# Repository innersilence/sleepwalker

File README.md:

sleepwalker
===========

Pulse and oximetry sensor and graphing software

AVR based wearable wireless sensor that sends pulse/blood oxigen level over wireless link to the collecting service.

Used to monitor blood oxigeneation to detect sleep apnea, REM periods.

LICENSE: MIT

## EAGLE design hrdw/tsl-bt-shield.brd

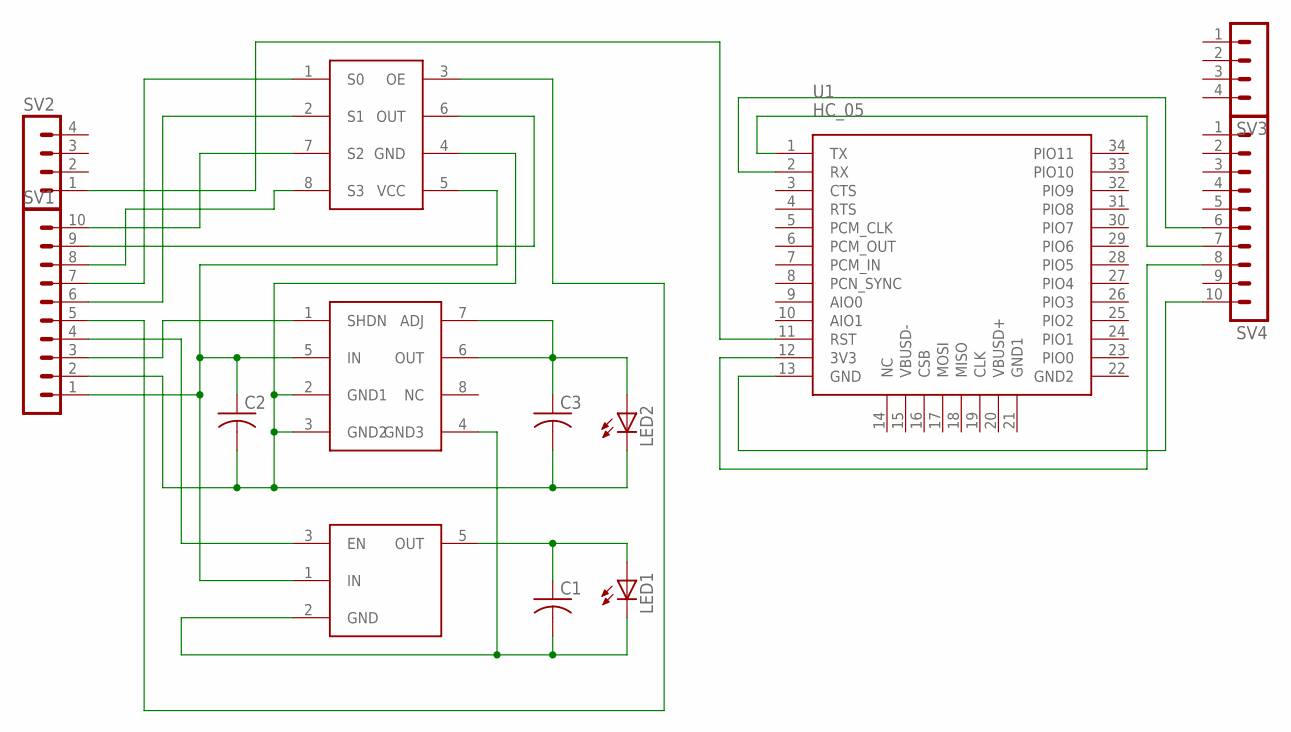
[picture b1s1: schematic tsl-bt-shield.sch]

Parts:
C1, C2, C3: C-USC1206K; C1206K
LED1, LED2: LED; SMARTLED-TTW
SV1, SV4: MA10-1
SV2, SV3: MA04-1
U1: HC_05; BLUETOOTH_SMD
U$1: LT3008; SOT23-8
U$2: TPS7701; SOT23-5
U$3: TSL230; TSL230-SOIC

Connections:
unnamed: C2.1, SV1.1, U$1.5 (IN), U$2.1 (IN), U$3.5 (VCC)
unnamed: C1.2, C2.2, C3.2, LED1.C@1 (C), LED2.C@1 (C), SV1.2, U$1.2 (GND1), U$1.3 (GND2), U$1.4 (GND3), U$2.2 (GND), U$3.4 (GND)
unnamed: C1.1, LED1.A@1 (A), U$2.5 (OUT)
unnamed: C3.1, LED2.A@1 (A), U$1.6 (OUT), U$1.7 (ADJ)
unnamed: SV1.4, U$2.3 (EN)
unnamed: SV1.3, U$1.1 (SHDN)
unnamed: SV1.9, U$3.6 (OUT)
unnamed: SV1.5, U$3.3 (OE)
unnamed: SV1.7, U$3.1 (S0)
unnamed: SV1.6, U$3.2 (S1)
unnamed: SV1.10, U$3.7 (S2)
unnamed: SV1.8, U$3.8 (S3)
unnamed: SV2.1, U1.11 (RST)
unnamed: SV4.10, U1.13 (GND)
unnamed: SV4.8, U1.12 (3V3)
unnamed: SV4.7, U1.1 (TX)
unnamed: SV4.6, U1.2 (RX)

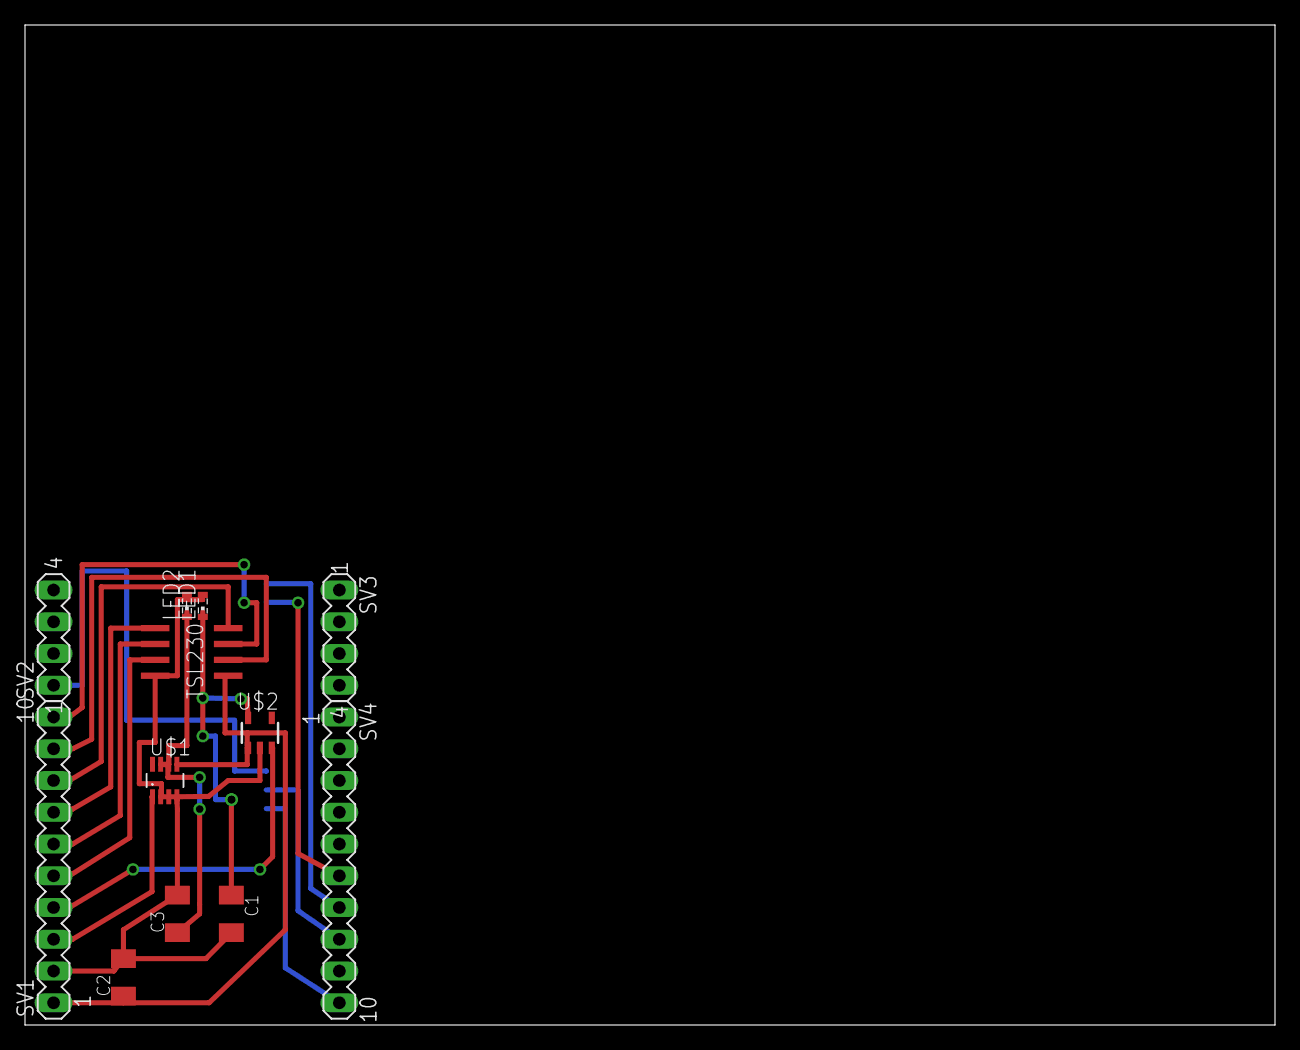
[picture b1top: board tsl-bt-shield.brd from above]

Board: 2 copper layers, 100.0 x 80.0 mm, 13 parts (1 on the bottom side), 17 nets.

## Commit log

2013-06-09 [sleepwalker] initial check-in of sensor code.
2013-06-10 [sleepwalker] some tsl320 and interrupt code added
2013-06-12 [sleepwalker] initial commit of port and timer files.
2013-06-12 [sleepwalker] truing to measure pulse width using timer.
2013-06-13 Current reg added
2013-06-13 [sleepwalker] license added and readme updated.
2013-06-13 [sleepwalker] license added.
2013-06-13 [sleepwalker] bom added.
2013-07-03 [sleepwalker] led, serial, and tsl230 pin interrupt code.
2013-07-03 [sleepwalker] more on timer interrupt handling.
2013-07-09 [sleepwalker] Changed pinout to match Arduino Fio, tested blinking led on PB.5
2013-07-20 [sleepwalker] code for blinking diagnostics, usart & bluetooth module init.
2013-07-25 [sleepwalker] usart and error blinker code changes.
2013-07-25 [sleepwalker] working suart code.
2013-07-25 [sleepwalker] cleaned up usart code.
2013-07-26 [sleepwalker] BT module shield designs added.
2013-08-30 [sleepwalker] changing name of BT device works.
2013-08-30 [sleepwalker] added tls init and other stuff..
2013-10-09 [sleepwalker] still working on reliable USART.
2013-10-10 [sleepwalker] usart ok, need to wait for battery to charge in full.
2013-10-15 [sleepwalker] bluetooth module works.
2013-11-25 [sleepwalker] tsl code working
2013-12-07 [sllepwalker] Monitor check-in.
2013-12-07 [sleepwalker] LED board pcb added.
2014-02-18 [sleepwalker] cleaning repo
2014-02-18 [sleepwaler] code cleanup.
2014-02-18 [sleepwalker] New monitor code added.
2014-02-18 [sleepwalker] hc-o6 Eagle lib added
2014-02-18 [sleepwalker] resizable graph
2014-02-25 [sleepwalker] peak detector implemented.
2014-02-27 [sleepwalker] implementing realtime grahing, work in progress
2014-02-27 [sleepwalekr] code cleanup
2014-02-27 [sleepwalker] ...
2014-03-07 [sleepwalker] Added lib for TSL230 & other
2014-03-07 [master] tsl shield schematics added.
2014-03-07 [master] updated package description in bom comments
2014-03-11 [master] TSL board design finalized
2014-03-25 [master] BOM updated
2014-03-25 [master] stuff...
